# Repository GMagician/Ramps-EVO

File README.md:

# Ramps-EVO
Shield for Grand Central M4 and Due

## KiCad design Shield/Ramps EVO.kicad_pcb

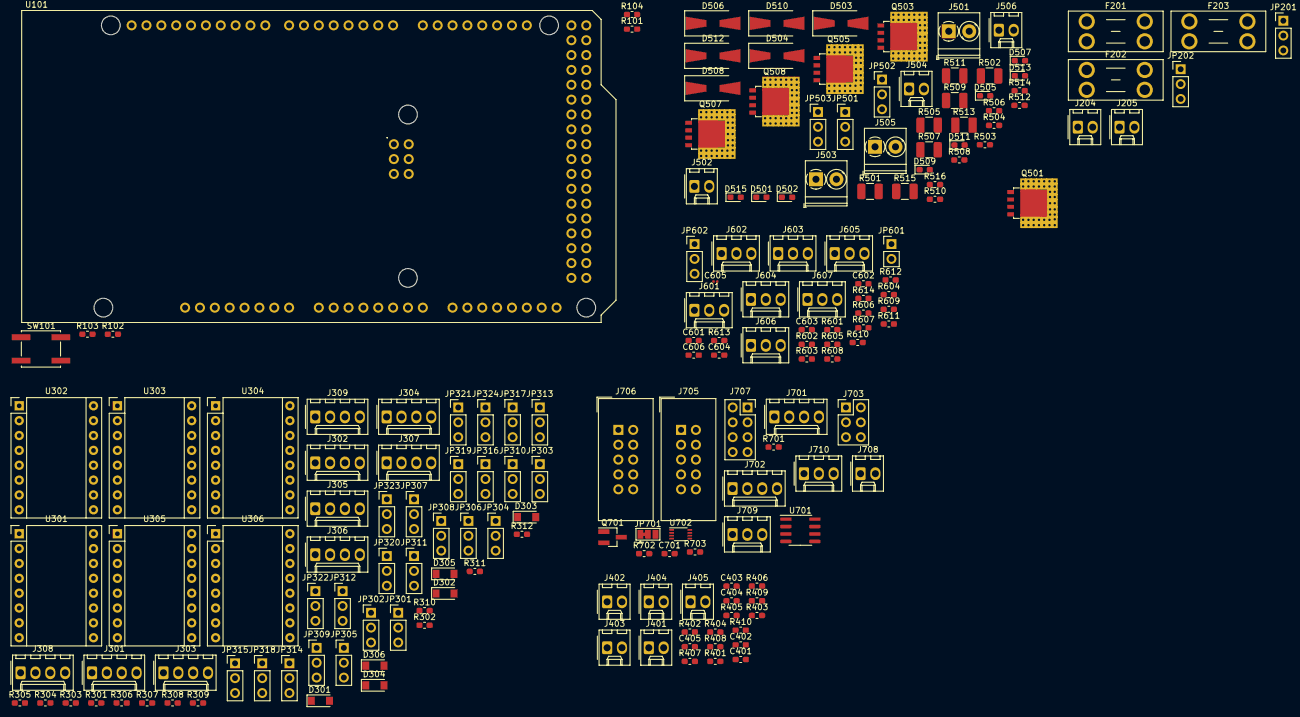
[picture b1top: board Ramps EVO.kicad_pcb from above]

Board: 2 copper layers, 180 parts (0 on the bottom side), 175 nets, no tracks yet.

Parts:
C401, C402, C403, C404, C405: 2u2; C_0603_1608Metric_Pad1.05x0.95mm_HandSolder
C601, C602, C603, C604, C606, C701: 100n; C_0603_1608Metric_Pad1.05x0.95mm_HandSolder
C605: 100n; C_0201_0603Metric
D301, D302, D303, D304, D305, D306: 3A 100V; D_SOD-123FL
D501, D502, D505, D507, D509, D511, D513, D515: LED_Small; LED_0603_1608Metric_Pad1.05x0.95mm_HandSolder
D503, D504, D506, D508, D510, D512: D_Schottky_Small_ALT; D_SMA-SMB_Universal_Handsoldering
F201: 10A; Fuseholder_Blade_Mini_Keystone_3568
F202: 15A; Fuseholder_Blade_Mini_Keystone_3568
F203: 25A; Fuseholder_Blade_Mini_Keystone_3568
J204: Ext 5V; Molex_KK-254_AE-6410-02A_1x02_P2.54mm_Vertical
J205: Ext 3V3; Molex_KK-254_AE-6410-02A_1x02_P2.54mm_Vertical
J301: XB; Molex_KK-254_AE-6410-04A_1x04_P2.54mm_Vertical
J302: XA; Molex_KK-254_AE-6410-04A_1x04_P2.54mm_Vertical
J303: E0; Molex_KK-254_AE-6410-04A_1x04_P2.54mm_Vertical
J304: YB; Molex_KK-254_AE-6410-04A_1x04_P2.54mm_Vertical
J305: YA; Molex_KK-254_AE-6410-04A_1x04_P2.54mm_Vertical
J306: E1; Molex_KK-254_AE-6410-04A_1x04_P2.54mm_Vertical
J307: ZB; Molex_KK-254_AE-6410-04A_1x04_P2.54mm_Vertical
J308: ZA; Molex_KK-254_AE-6410-04A_1x04_P2.54mm_Vertical
J309: E2; Molex_KK-254_AE-6410-04A_1x04_P2.54mm_Vertical
J401: TH0; Molex_KK-254_AE-6410-02A_1x02_P2.54mm_Vertical
J402: TH1; Molex_KK-254_AE-6410-02A_1x02_P2.54mm_Vertical
J403: TH2; Molex_KK-254_AE-6410-02A_1x02_P2.54mm_Vertical
J404: TH3; Molex_KK-254_AE-6410-02A_1x02_P2.54mm_Vertical
J405: TH4; Molex_KK-254_AE-6410-02A_1x02_P2.54mm_Vertical
J501: HE0; TerminalBlock_Phoenix_PT-1,5-2-3.5-H_1x02_P3.50mm_Horizontal
J502: FAN0; Molex_KK-254_AE-6410-02A_1x02_P2.54mm_Vertical
J503: HE1; TerminalBlock_Phoenix_PT-1,5-2-3.5-H_1x02_P3.50mm_Horizontal
J504: FAN1; Molex_KK-254_AE-6410-02A_1x02_P2.54mm_Vertical
J505: HE2; TerminalBlock_Phoenix_PT-1,5-2-3.5-H_1x02_P3.50mm_Horizontal
J506: FAN2; Molex_KK-254_AE-6410-02A_1x02_P2.54mm_Vertical
J601: XMIN; Molex_KK-254_AE-6410-03A_1x03_P2.54mm_Vertical
J602: XMAX; Molex_KK-254_AE-6410-03A_1x03_P2.54mm_Vertical
J603: ZPROBE; Molex_KK-254_AE-6410-03A_1x03_P2.54mm_Vertical
J604: YMIN; Molex_KK-254_AE-6410-03A_1x03_P2.54mm_Vertical
J605: YMAX; Molex_KK-254_AE-6410-03A_1x03_P2.54mm_Vertical
J606: ZMIN; Molex_KK-254_AE-6410-03A_1x03_P2.54mm_Vertical
J607: ZMAX; Molex_KK-254_AE-6410-03A_1x03_P2.54mm_Vertical
J701: I2C; Molex_KK-254_AE-6410-04A_1x04_P2.54mm_Vertical
J702: NEXTION; Molex_KK-254_AE-6410-04A_1x04_P2.54mm_Vertical
J703: SPI; PinHeader_2x03_P2.54mm_Vertical
J705, J706: EXP1; IDC-Header_2x05_P2.54mm_Vertical
J707: ESP8266; PinSocket_2x04_P2.54mm_Vertical
J708: PWRFAIL; Molex_KK-254_AE-6410-02A_1x02_P2.54mm_Vertical
J709: SERVO0; Molex_KK-254_AE-6410-03A_1x03_P2.54mm_Vertical
J710: SERVO1; Molex_KK-254_AE-6410-03A_1x03_P2.54mm_Vertical
JP201, JP202, JP301, JP302, JP303, JP304, JP305, JP306, JP307, JP308, JP309, JP310, JP311, JP312, JP313, JP314, JP315, JP316, JP317, JP318, JP319, JP320, JP321, JP322, JP323, JP324, JP501, JP502, JP503, JP602: Jumper_3_Open; PinHeader_1x03_P2.54mm_Vertical
JP601: Jumper_NO_Small; PinHeader_1x02_P2.54mm_Vertical
JP701: SolderJumper_3_Bridged123; SolderJumper-3_P1.3mm_Bridged12_Pad1.0x1.5mm
Q501, Q503, Q505: BUK9Y14-40B; LFPAK56_ThermalVias-1
Q507, Q508: PSMN1R8-40YLC; LFPAK56_ThermalVias-1
Q701: AO3400; SOT-23_Handsoldering
R101, R102: 2K2; R_0603_1608Metric_Pad1.05x0.95mm_HandSolder
R103, R104: 22R; R_0603_1608Metric_Pad1.05x0.95mm_HandSolder
R301, R302, R305, R306, R309, R310, R601, R602, R603, R604, R606, R607, R609, R610, R611, R612, R613, R614: 10k; R_0603_1608Metric_Pad1.05x0.95mm_HandSolder
R303, R304, R307, R308, R311, R312: 100k; R_0603_1608Metric_Pad1.05x0.95mm_HandSolder
R401, R402, R403, R404, R405: 4K7 0.1%; R_0603_1608Metric_Pad1.05x0.95mm_HandSolder
R406, R407, R408, R409, R410: 10K; R_0603_1608Metric_Pad1.05x0.95mm_HandSolder
R501, R502, R505, R507, R509, R511, R513, R515: 2K2; R_1210_3225Metric_Pad1.42x2.65mm_HandSolder
R503, R504, R506, R508, R510, R512, R514, R516, R608, R701, R703: 22K; R_0603_1608Metric_Pad1.05x0.95mm_HandSolder
R605: ?K; R_0603_1608Metric_Pad1.05x0.95mm_HandSolder
R702: 10R; R_0603_1608Metric_Pad1.05x0.95mm_HandSolder
SW101: RST; SW_SPST_EVQQ2
U101: Grand-Central-M4; Grand-Central-M4_Shield
U301: X; Pololu_Breakout-16_15.2x20.3mm
U302: E0; Pololu_Breakout-16_15.2x20.3mm
U303: Y; Pololu_Breakout-16_15.2x20.3mm
U304: E1; Pololu_Breakout-16_15.2x20.3mm
U305: Z; Pololu_Breakout-16_15.2x20.3mm
U306: E2; Pololu_Breakout-16_15.2x20.3mm
U701: 24LC256; SOIC-8_3.9x4.9mm_P1.27mm
U702: TXS0102DCU; VSSOP-8_2.3x2mm_P0.5mm

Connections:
+3V3: C701.1, D301.2, D302.2, D303.2, D304.2, D305.2, D306.2, J601.2, J602.2, J604.2, J605.2, J606.2, J607.2, J701.1, J703.1, J707.4, J707.8, J709.2, J710.2, JP202.2, JP301.1, JP302.1, JP303.1, JP304.1, JP305.1, JP306.1, JP309.1, JP310.1, JP311.1, JP312.1, JP313.1, JP314.1, JP317.1, JP318.1, JP319.1, JP320.1, JP321.1, JP322.1, JP601.1, JP701.3, R101.2, R102.2, R301.2, R302.2, R305.2, R306.2, R309.2, R310.2, U301.10, U302.10, U303.10, U304.10, U305.10, U306.10, U701.8, U702.3, U702.6
+5V: J702.1, J705.10, JP201.2, U702.7
+5VI: JP201.1, JP202.1, JP501.1, JP502.1, JP503.1, JP602.1, U101.VIN
+VBED: F203.2, R513.2, R515.2
+VMOT: D301.1, D302.1, D303.1, D304.1, D305.1, D306.1, F202.2, U301.16, U302.16, U303.16, U304.16, U305.16, U306.16
+VPWR: D503.1, D506.1, D510.1, F201.2, J501.1, J503.1, J505.1, JP501.3, JP502.3, JP503.3, JP602.3, R501.2, R505.2, R509.2
/Devices/RX: J702.3, U702.1
/Devices/TX: J702.2, U702.8
/SCL-D21: R104.2, U101.D21
/SDA-D20: R103.2, U101.D20
ADVREF: R401.2, R402.2, R403.2, R404.2, R405.2, U101.3V3
E0_DIR: U101.D28, U302.8
E0_EN: R302.1, U101.D33, U302.1
E0_SPICS: JP306.3, U101.A14
E0_STEP: U101.D29, U302.7
E1_DIR: U101.D24, U304.8
E1_EN: R306.1, U101.D26, U304.1
E1_SPICS: JP314.3, U101.A15
E1_STEP: U101.D22, U304.7
E2_DIR: U101.D23, U306.8
E2_EN: R310.1, U101.D27, U306.1
E2_SPICS: JP322.3, U101.D53
E2_STEP: U101.D25, U306.7
ESP8266_RX: J707.2, U101.D16
ESP8266_TX: J707.7, U101.D17
FAN0: R504.1, U101.D9
FAN1: R508.1, U101.D8
FAN2: R512.1, U101.D10
GND: C401.2, C402.2, C403.2, C404.2, C405.2, C601.2, C602.2, C603.2, C604.2, C605.2, C606.2, C701.2, J204.2, J205.2, J401.1, J402.1, J403.1, J404.1, J405.1, J601.3, J602.3, J603.3, J604.3, J605.3, J606.3, J607.3, J701.2, J702.4, J703.6, J705.9, J706.9, J707.1, J708.2, J709.3, J710.3, JP701.1, Q501.1, Q501.2, Q501.3, Q503.1, Q503.2, Q503.3, Q505.1, Q505.2, Q505.3, Q507.1, Q507.2, Q507.3, Q508.1, Q508.2, Q508.3, Q701.2, R303.1, R304.1, R307.1, R308.1, R311.1, R312.1, R503.2, R504.2, R506.1, R508.2, R510.2, R512.2, R514.2, R516.2, R608.2, R701.1, R703.1, SW101.2, U101.GND1, U101.GND2, U101.GND3, U101.GND4, U101.GND5, U101.GND6, U301.9, U301.15, U302.9, U302.15, U303.9, U303.15, U304.9, U304.15, U305.9, U305.15, U306.9, U306.15, U701.2, U701.3, U701.4, U701.7, U702.2
HEAT0: Q501.4, R503.1, U101.D13
HEAT1: Q503.4, R506.2, U101.D12
HEAT2: Q505.4, R510.1, U101.D11
HEATBED0: Q507.4, R514.1, U101.D7
HEATBED1: Q508.4, R516.1, U101.D6
LCD_BEEP: J705.1, R701.2, U101.A8
LCD_D4-CLK: J705.5, U101.D14
LCD_D5: J705.6, U101.A7
LCD_D6: J705.7, U101.D19, U702.5
LCD_D7: J705.8, U101.D18, U702.4
LCD_E-SID: J705.3, U101.A10
LCD_ENCA: J706.5, U101.D44
LCD_ENCB: J706.3, U101.D42
LCD_ENCBTN: J705.2, U101.D40
LCD_RS-CS: J705.4, U101.A9
LCD_STOPBTN: J706.8, U101.A11
MISO: J703.2, J706.1, JP307.3, JP308.3, JP315.3, JP316.3, JP323.3, JP324.3, U101.MISO
MOSI: J703.4, J706.6, JP301.3, JP302.3, JP309.3, JP310.3, JP317.3, JP318.3, U101.MOSI
unnamed: D501.1, D503.2, J501.2, Q501.5
unnamed: D501.2, R501.1
unnamed: D502.1, D504.2, J502.2
unnamed: D502.2, R502.1
unnamed: D504.1, J502.1, JP501.2, R502.2
unnamed: D505.1, D506.2, J503.2, Q503.5
unnamed: D505.2, R505.1
unnamed: D507.1, D508.2, J504.2
unnamed: D507.2, R507.1
unnamed: D508.1, J504.1, JP502.2, R507.2
unnamed: D509.1, D510.2, J505.2, Q505.5
unnamed: D509.2, R509.1
unnamed: D511.1, D512.2, J506.2
unnamed: D511.2, R511.1
unnamed: D512.1, J506.1, JP503.2, R511.2
unnamed: D513.1, Q507.5
unnamed: D513.2, R513.1
unnamed: D515.1, Q508.5
unnamed: D515.2, R515.1
unnamed: J204.1, JP201.3
unnamed: J205.1, JP202.3
unnamed: J301.1, J302.2
unnamed: J301.2, U301.12
unnamed: J301.3, J302.4
unnamed: J301.4, U301.14
unnamed: J302.1, U301.11
unnamed: J302.3, U301.13
unnamed: J303.1, U302.11
unnamed: J303.2, U302.12
unnamed: J303.3, U302.13
unnamed: J303.4, U302.14
unnamed: J304.1, J305.2
unnamed: J304.2, U303.12
unnamed: J304.3, J305.4
unnamed: J304.4, U303.14
unnamed: J305.1, U303.11
unnamed: J305.3, U303.13
unnamed: J306.1, U304.11
unnamed: J306.2, U304.12
unnamed: J306.3, U304.13
unnamed: J306.4, U304.14
unnamed: J307.1, J308.2
unnamed: J307.2, U305.12
unnamed: J307.3, J308.4
unnamed: J307.4, U305.14
unnamed: J308.1, U305.11
unnamed: J308.3, U305.13
unnamed: J309.1, U306.11
unnamed: J309.2, U306.12
unnamed: J309.3, U306.13
unnamed: J309.4, U306.14
unnamed: J401.2, R405.1, R406.2
unnamed: J402.2, R404.1, R407.2
unnamed: J403.2, R403.1, R408.2
unnamed: J404.2, R402.1, R409.2
unnamed: J405.2, R401.1, R410.2
unnamed: J601.1, R603.2
unnamed: J602.1, R604.2
unnamed: J603.1, R605.1, R608.1
unnamed: J603.2, JP602.2
unnamed: J604.1, R609.2
unnamed: J605.1, R610.2
unnamed: J606.1, R613.2
unnamed: J607.1, R614.2
unnamed: JP301.2, R303.2, U301.2
unnamed: JP302.2, R304.2, U302.2
unnamed: JP303.2, U301.3
unnamed: JP304.2, U302.3
unnamed: JP305.2, U301.4
unnamed: JP306.2, U302.4
unnamed: JP307.1, U301.6
unnamed: JP307.2, U301.5
unnamed: JP308.1, U302.6
unnamed: JP308.2, U302.5
unnamed: JP309.2, R307.2, U303.2
unnamed: JP310.2, R308.2, U304.2
unnamed: JP311.2, U303.3
unnamed: JP312.2, U304.3
unnamed: JP313.2, U303.4
unnamed: JP314.2, U304.4
unnamed: JP315.1, U303.6
unnamed: JP315.2, U303.5
unnamed: JP316.1, U304.6
unnamed: JP316.2, U304.5
unnamed: JP317.2, R311.2, U305.2
unnamed: JP318.2, R312.2, U306.2
unnamed: JP319.2, U305.3
unnamed: JP320.2, U306.3
unnamed: JP321.2, U305.4
unnamed: JP322.2, U306.4
unnamed: JP323.1, U305.6
unnamed: JP323.2, U305.5
unnamed: JP324.1, U306.6
unnamed: JP324.2, U306.5
unnamed: JP601.2, R601.2, R602.2, R606.2, R607.2, R611.2, R612.2
unnamed: JP701.2, U701.1
unnamed: Q701.3, R702.2
PS_ON: Q701.1, R703.2, U101.A13
PWR_FAIL: J708.1, U101.D15
RESET: J707.6, SW101.1, U101.~RST2
SCK: J703.5, J706.2, JP303.3, JP304.3, JP311.3, JP312.3, JP319.3, JP320.3, U101.SCK
SCL: J701.4, R102.1, R104.1, U701.6
SDA: J701.3, R101.1, R103.1, U701.5
SDCS: J706.4, U101.D4
SD_DETECT: J706.7, U101.D39
SERVO0: J709.1, U101.D5
SERVO1: J710.1, U101.D3
THERMISTOR0: C405.1, R406.1, U101.A0
THERMISTOR1: C404.1, R407.1, U101.A1
THERMISTOR2: C403.1, R408.1, U101.A2
THERMISTOR3: C402.1, R409.1, U101.A3
THERMISTOR4: C401.1, R410.1, U101.A4
XYZ_EN: R301.1, R305.1, R309.1, U101.D31, U301.1, U303.1, U305.1
X_DIR: U101.D36, U301.8
X_MAX: C602.1, R602.1, R604.1, U101.D48
X_MIN: C601.1, R601.1, R603.1, U101.D45
X_SPICS: JP305.3, U101.D38
X_STEP: U101.D37, U301.7
Y_DIR: U101.D35, U303.8
Y_MAX: C604.1, R607.1, R610.1, U101.D41
Y_MIN: C603.1, R606.1, R609.1, U101.D46
Y_SPICS: JP313.3, U101.D34
Y_STEP: U101.D32, U303.7
Z_DIR: U101.D2, U305.8
Z_MAX: C606.1, R612.1, R614.1, U101.D43
Z_MIN: C605.1, R611.1, R613.1, U101.D47
Z_SPICS: JP321.3, U101.A12
Z_STEP: U101.D30, U305.7

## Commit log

2020-07-27 Genesis
